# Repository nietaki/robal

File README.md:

# Robal

## License

[robal](https://github.com/nietaki/robal](https://github.com/nietaki/robal) is licensed under [CC BY-SA 4.0](http://creativecommons.org/licenses/by-sa/4.0/?ref=chooser-v1)

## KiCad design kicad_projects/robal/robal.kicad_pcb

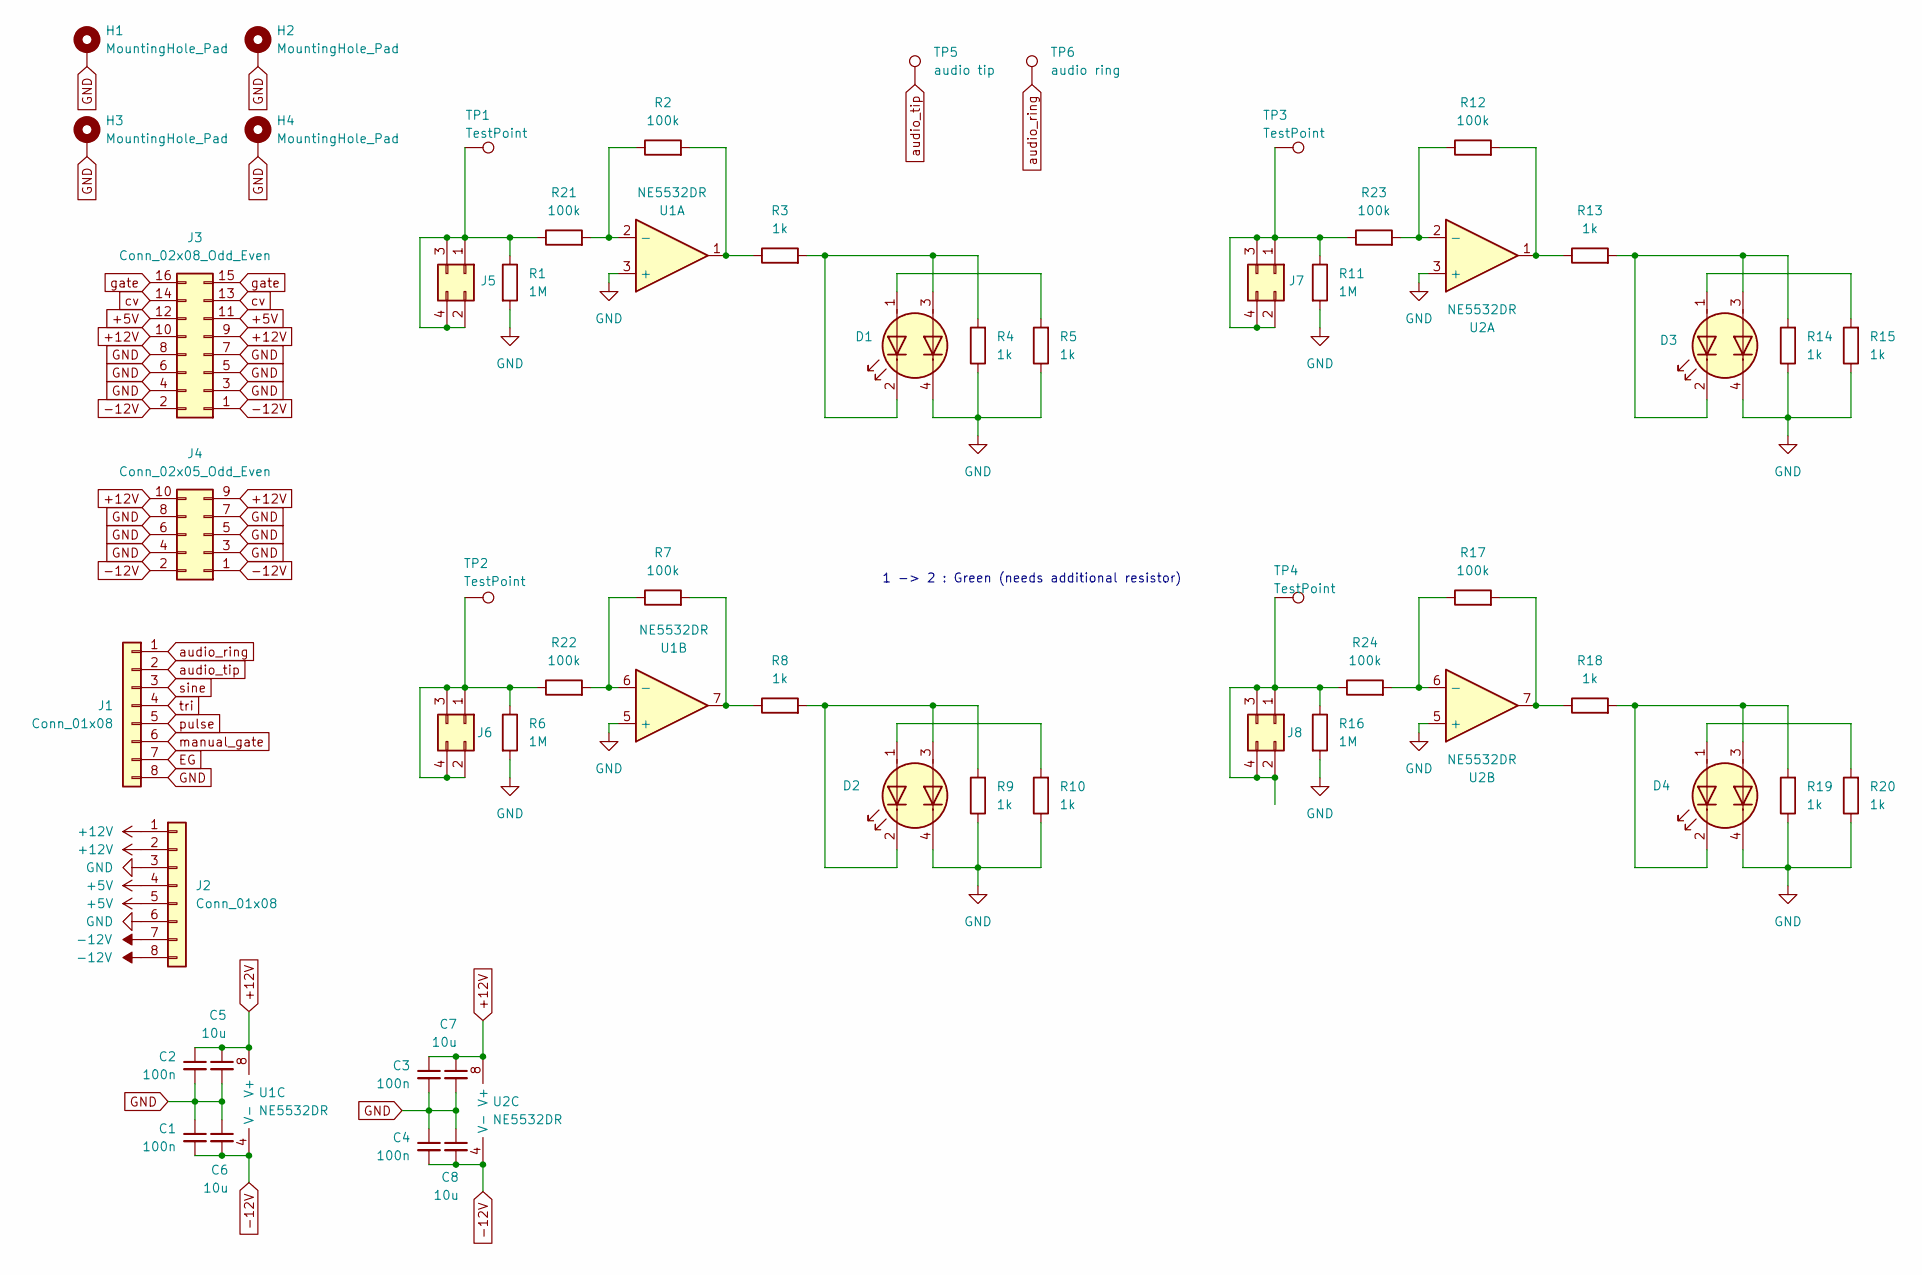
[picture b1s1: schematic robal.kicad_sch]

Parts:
C1, C2, C3, C4: 100n; C_0603_1608Metric; LCSC PN C14663
C5, C6, C7, C8: 10u; C_0805_2012Metric; LCSC PN C15850
D1, D2, D3, D4: LED_Dual_AKAK; E6C1209RVGC2UDA; LCSC PN C375560
H1, H2, H3, H4: MountingHole_Pad; MountingHole_3.5mm_Pad_TopBottom
J1, J2: Conn_01x08; PinHeader_1x08_P2.54mm_Vertical
J3: Conn_02x08_Odd_Even; IDC-Header_2x08_P2.54mm_Vertical
J4: Conn_02x05_Odd_Even; IDC-Header_2x05_P2.54mm_Vertical
J5, J6, J7, J8: Conn_02x02_Odd_Even; PinSocket_2x02_P2.54mm_Vertical
R1, R6, R11, R16: 1M; R_0603_1608Metric; LCSC PN C22935
R2, R7, R12, R17, R21, R22, R23, R24: 100k; R_0603_1608Metric; LCSC PN C25803
R3, R4, R5, R8, R9, R10, R13, R14, R15, R18, R19, R20: 1k; R_0603_1608Metric; LCSC PN C21190
TP1, TP2, TP3, TP4: TestPoint; TestPoint_Loop_D3.50mm_Drill1.4mm_Beaded
TP5: audio tip; TestPoint_Loop_D3.50mm_Drill1.4mm_Beaded
TP6: audio ring; TestPoint_Loop_D3.50mm_Drill1.4mm_Beaded
U1, U2: NE5532DR; SOIC-8_3.9x4.9mm_P1.27mm; LCSC PN C7426

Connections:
+5V: J2.4, J2.5, J3.11, J3.12
+12V: C2.1, C3.1, C5.1, C7.1, J2.1, J2.2, J3.9, J3.10, J4.9, J4.10, U1.8 (V+), U2.8 (V+)
-12V: C1.2, C4.2, C6.2, C8.2, J2.7, J2.8, J3.1, J3.2, J4.1, J4.2, U1.4 (V-), U2.4 (V-)
EG: J1.7
GND: C1.1, C2.2, C3.2, C4.1, C5.2, C6.1, C7.2, C8.1, D1.4 (K2), D2.4 (K2), D3.4 (K2), D4.4 (K2), H1.1, H2.1, H3.1, H4.1, J1.8, J2.3, J2.6, J3.3, J3.4, J3.5, J3.6, J3.7, J3.8, J4.3, J4.4, J4.5, J4.6, J4.7, J4.8, R1.2, R4.1, R5.1, R6.2, R9.1, R10.1, R11.2, R14.1, R15.1, R16.2, R19.1, R20.1, U1.3 (+), U1.5 (+), U2.3 (+), U2.5 (+)
unnamed: D1.1 (A1), R5.2
unnamed: D1.2 (K1), D1.3 (A2), R3.2, R4.2
unnamed: D2.1 (A1), R10.2
unnamed: D2.2 (K1), D2.3 (A2), R8.2, R9.2
unnamed: D3.1 (A1), R15.2
unnamed: D3.2 (K1), D3.3 (A2), R13.2, R14.2
unnamed: D4.1 (A1), R20.2
unnamed: D4.2 (K1), D4.3 (A2), R18.2, R19.2
unnamed: J5.1, J5.2, J5.3, J5.4, R1.1, R21.1, TP1.1
unnamed: J6.1, J6.2, J6.3, J6.4, R6.1, R22.1, TP2.1
unnamed: J7.1, J7.2, J7.3, J7.4, R11.1, R23.1, TP3.1
unnamed: J8.1, J8.2, J8.3, J8.4, R16.1, R24.1, TP4.1
unnamed: R2.2, R3.1, U1.1
unnamed: R7.2, R8.1, U1.7
unnamed: R12.2, R13.1, U2.1
unnamed: R17.2, R18.1, U2.7
unnamed: R2.1, R21.2, U1.2 (-)
unnamed: R7.1, R22.2, U1.6 (-)
unnamed: R12.1, R23.2, U2.2 (-)
unnamed: R17.1, R24.2, U2.6 (-)
audio_ring: J1.1, TP6.1
audio_tip: J1.2, TP5.1
cv: J3.13, J3.14
gate: J3.15, J3.16
manual_gate: J1.6
pulse: J1.5
sine: J1.3
tri: J1.4

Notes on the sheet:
1 -> 2 : Green (needs additional resistor)

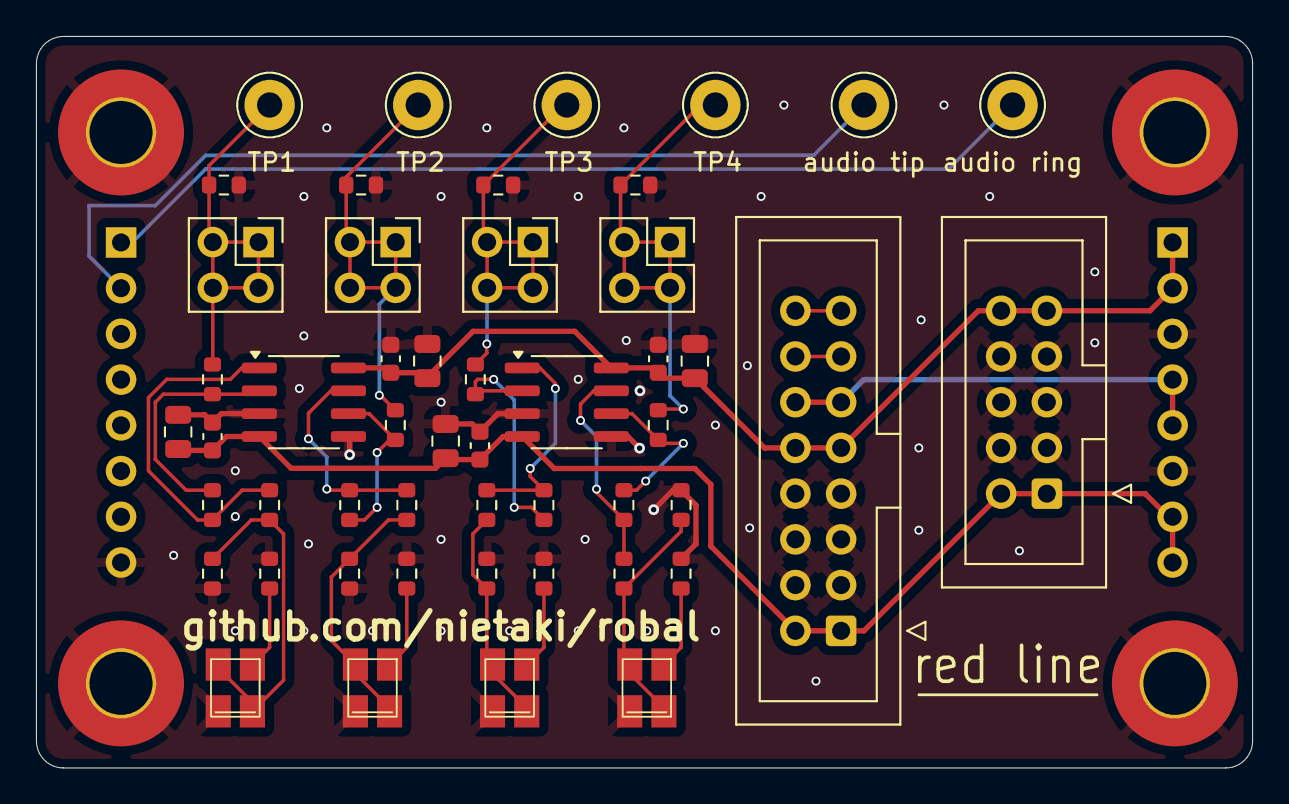
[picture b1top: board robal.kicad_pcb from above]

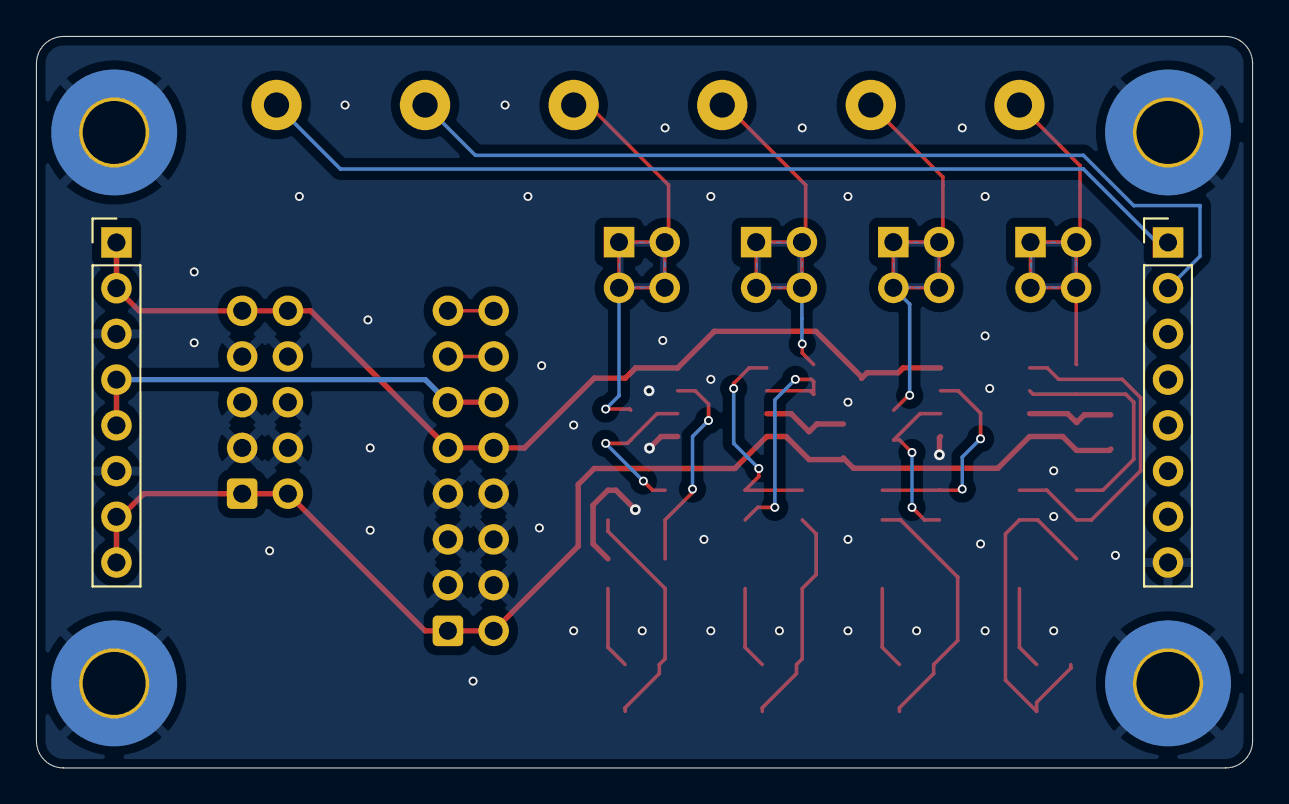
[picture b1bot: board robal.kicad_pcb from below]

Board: 2 copper layers, 67.6 x 40.6 mm, 56 parts (2 on the bottom side), 28 nets.

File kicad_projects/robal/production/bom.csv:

Designator,Footprint,Quantity,Value,LCSC Part #
"C1, C2, C3, C4",0603,4,100n,
"C5, C6, C7, C8",0805,4,10u,
"D1, D2, D3, D4",E6C1209RVGC2UDA,4,LED_Dual_AKAK,
"J1, J2",PinHeader_1x08_P2.54mm_Vertical,2,Conn_01x08,
J3,IDC-Header_2x08_P2.54mm_Vertical,1,Conn_02x08_Odd_Even,
J4,IDC-Header_2x05_P2.54mm_Vertical,1,Conn_02x05_Odd_Even,
"J5, J6, J7, J8",PinSocket_2x02_P2.54mm_Vertical,4,Conn_02x02_Odd_Even,
"R1, R11, R16, R6",0603,4,1M,
"R10, R13, R14, R15, R18, R19, R20, R3, R4, R5, R8, R9",0603,12,1k,
"R12, R17, R2, R21, R22, R23, R24, R7",0603,8,100k,
"TP1, TP2, TP3, TP4",TestPoint_Loop_D3.50mm_Drill1.4mm_Beaded,4,TestPoint,
TP5,TestPoint_Loop_D3.50mm_Drill1.4mm_Beaded,1,audio tip,
TP6,TestPoint_Loop_D3.50mm_Drill1.4mm_Beaded,1,audio ring,
"U1, U2",SOIC-8_3.9x4.9mm_P1.27mm,2,NE5532DR,

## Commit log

2025-05-12 Better decoupling caps, red line marker, removed part designators
